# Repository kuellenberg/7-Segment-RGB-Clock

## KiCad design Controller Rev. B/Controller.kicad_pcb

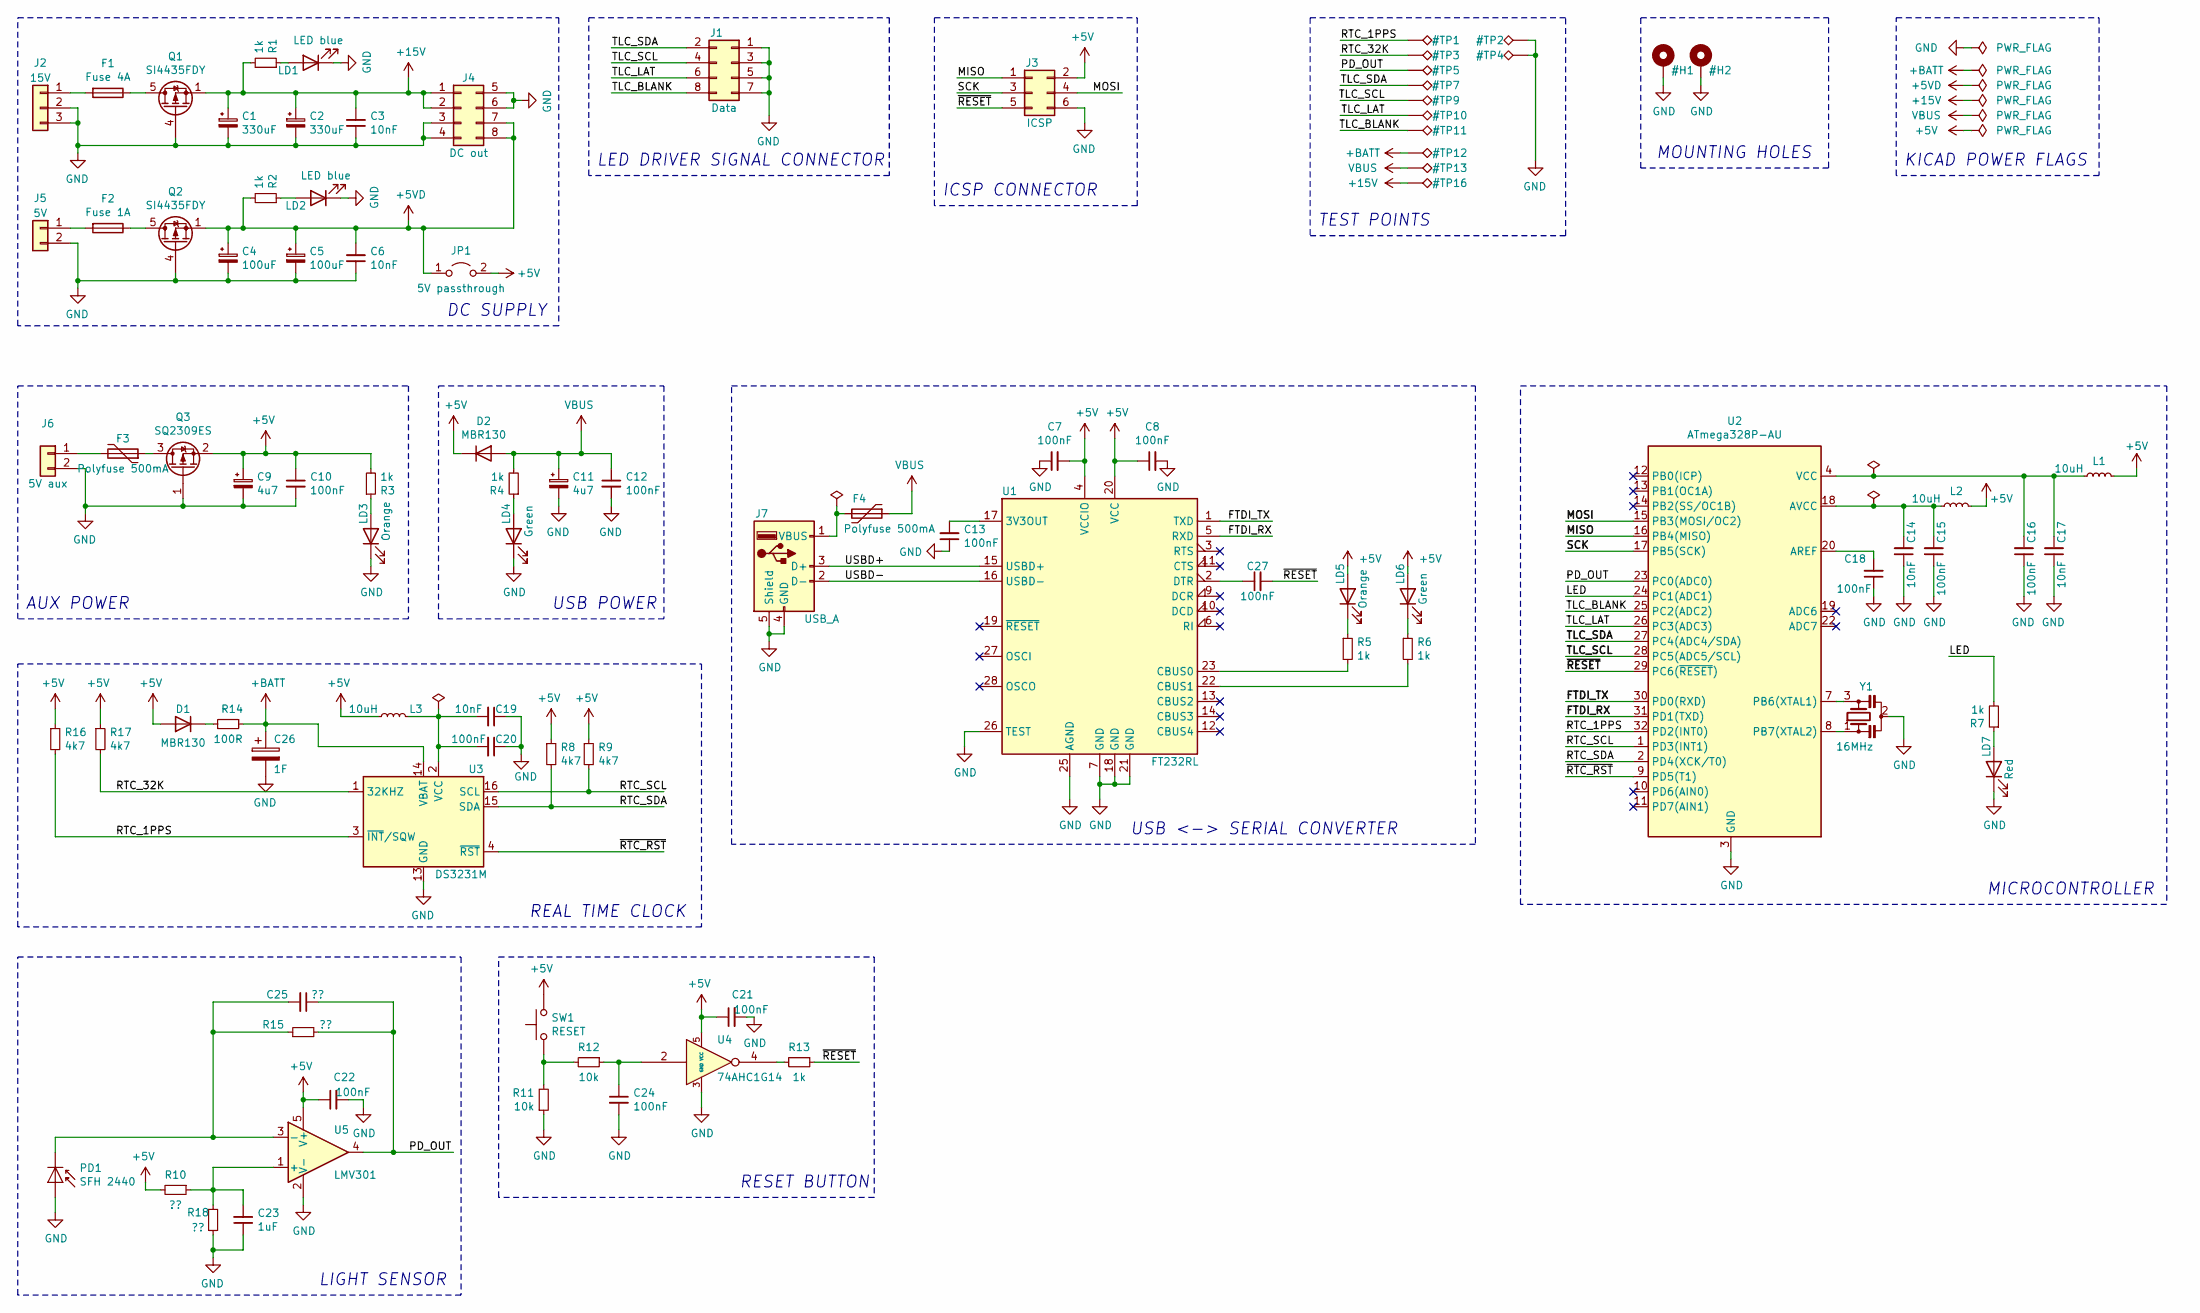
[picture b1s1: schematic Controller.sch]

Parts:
C1, C2: 330uF; CP_Elec_10x10; Mouser 661-EMVE250ADA331MJA
C3: 10nF; C_0805_2012Metric; Mouser 710-885012207092
C4, C5: 100uF; C_Elec_6.3x5.8; Mouser 647-UUR1A101MCL1GS
C6, C14, C17, C19: 10nF; C_0603_1608Metric; Mouser 710-885012206089
C7, C8, C10, C12, C13, C15, C16, C18, C20, C21, C22, C24, C27: 100nF; C_0603_1608Metric; Mouser 576-1812L050PR
C9, C11: 4u7; C_Elec_4x5.8; Mouser 667-EEE-FK1K4R7P
C23: 1uF; C_0603_1608Metric; Mouser 963-TMK107B7105MA-T
C25: ??; C_0603_1608Metric
C26: 1F; FC0H105ZFTBR44; Mouser 80-FC0H105ZFTBR44-SS
D1, D2: MBR130; D_SOD-123; Mouser 863-MBR130T1G
F1: Fuse 4A; Fuseholder_SMD_Littelfuse_154; Mouser 576-0154004.DRT
F2: Fuse 1A; Fuseholder_SMD_Littelfuse_154; Mouser 576-0154001.DR
F3, F4: Polyfuse 500mA; Fuse_1812_4532Metric; Mouser 576-1812L050PR
J1, J4: Conn_02x04_Top_Bottom; HARWIN_M20-8890845; Mouser 855-M20-8890845
J2: 15V; JST_XH_B03B-XH-A_03x2.50mm_Straight; Digikey 455-2248-ND
J3: Conn_02x03_Top_Bottom; IDC-Header_2x03_P2.54mm_Vertical; Digikey 732-5394-ND
J5: 5V; JST_XH_B2B-XH-A_1x02_P2.50mm_Vertical; Digikey 455-2247-ND
J6: Conn_01x02; JST_XH_B2B-XH-A_1x02_P2.50mm_Vertical; Digikey 455-2247-ND
J7: USB_A; USB_B_OST_USB-B1HSxx_Horizontal; Mouser 649-61729-0011BLF
JP1: Jumper; PinSocket_1x02_P2.54mm_Vertical; Digikey S1012EC-02-ND
L1, L2, L3: 10uH; L_0805_2012Metric; Mouser 963-LBR2012T100K
LD1, LD2: LED blue; LED_0603_1608Metric; Mouser 859-LTSTC193TBKT5A
LD3, LD5: LED; LED_0603_1608Metric; Mouser 859-LTST-C191KFKT
LD4, LD6: LED; LED_0603_1608Metric; Mouser 859-LTST-C190KGKT
LD7: LED; LED_0603_1608Metric; Mouser 859-LTST-C190KRKT
PD1: SFH 2440; Osram_SMD-DIL2_4.5x4.0mm; Mouser 720-SFH2440
Q1, Q2: SI4435FDY; SO-8_5.3x6.2mm_P1.27mm; Mouser 78-SI4435FDY-T1-GE3
Q3: SQ2309ES; SOT-23; Mouser 781-SQ2309ES-T1_GE3
R1, R2, R3, R4, R5, R6, R7, R13: 1k; R_0603_1608Metric; Mouser 660-RN73H1JT1001F100
R8, R9, R16, R17: 4k7; R_0603_1608Metric; Mouser 660-RN73H1JT4701F100
R10, R15, R18: ??; R_0603_1608Metric
R11, R12: 10k; R_0603_1608Metric; Mouser 660-RN73H1JTD1002F50
R14: 100R; R_0603_1608Metric; Mouser 660-RN73H1JT1000F100
SW1: RESET; SW_PUSH_6mm
U1: FT232RL; SSOP-28_5.3x10.2mm_P0.65mm; Mouser 895-FT232RL
U2: ATmega328P-AU; TQFP-32_7x7mm_P0.8mm; Mouser 556-ATMEGA328P-AU
U3: DS3231M; SOIC-16W_7.5x10.3mm_P1.27mm; Mouser 700-DS3231M+TRL
U4: 74AHC1G14; SOT-23-5; Mouser 595-SN74AHC1G14DBVR
U5: LMV301; SOT-353_SC-70-5; Mouser 926-LMV301MGX/NOPB
Y1: 16MHz; CSTNE; Mouser 81-CSTNE16M0V53Z000R

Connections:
+5V: C7.2, C8.1, C9.1, C10.1, C21.1, C22.1, D1.2 (A), D2.1 (K), J3.2, JP1.2 (B), L1.2, L2.2, L3.1, LD5.2 (A), LD6.2 (A), Q3.2 (S), R3.2, R8.1, R9.1, R10.2, R16.1, R17.1, SW1.2, U1.4 (VCCIO), U1.20 (VCC), U4.5 (VCC), U5.5 (V+)
+5VD: C4.1, C5.1, C6.2, J4.7, J4.8, JP1.1 (A), Q2.1 (S), Q2.2 (S), Q2.3 (S), R2.2
+15V: C1.1, C2.1, C3.2, J4.1, J4.2, Q1.1 (S), Q1.2 (S), Q1.3 (S), R1.2; also elsewhere on the board
+BATT: C26.1, R14.1, U3.14 (VBAT); also elsewhere on the board
/FTDI_RX: U1.5 (RXD), U2.31 (PD1(TXD))
/FTDI_TX: U1.1 (TXD), U2.30 (PD0(RXD))
/LED: R7.2, U2.24 (PC1(ADC1))
/MISO: J3.1, U2.16 (PB4(MISO))
/MOSI: J3.4, U2.15 (PB3(MOSI/OC2))
/PD_OUT: C25.1, R15.2, U2.23 (PC0(ADC0)), U5.4; also elsewhere on the board
/RTC_1PPS: R16.2, U2.32 (PD2(INT0)), U3.3 (~INT~/SQW); also elsewhere on the board
/RTC_32K: R17.2, U3.1 (32KHZ); also elsewhere on the board
/RTC_SCL: R9.2, U2.1 (PD3(INT1)), U3.16 (SCL)
/RTC_SDA: R8.2, U2.2 (PD4(XCK/T0)), U3.15 (SDA)
/SCK: J3.3, U2.17 (PB5(SCK))
/TLC_BLANK: J1.8, U2.25 (PC2(ADC2)); also elsewhere on the board
/TLC_LAT: J1.6, U2.26 (PC3(ADC3)); also elsewhere on the board
/TLC_SCL: J1.4, U2.28 (PC5(ADC5/SCL)); also elsewhere on the board
/TLC_SDA: J1.2, U2.27 (PC4(ADC4/SDA)); also elsewhere on the board
/USBD+: J7.3 (D+), U1.15 (USBD+)
/USBD-: J7.2 (D-), U1.16 (USBD-)
/~RESET~: C27.2, J3.5, R13.1, U2.29 (PC6(~RESET~))
/~RTC_RST~: U2.9 (PD5(T1)), U3.4 (~RST)
GND: C1.2, C2.2, C3.1, C4.2, C5.2, C6.1, C7.1, C8.2, C9.2, C10.2, C11.2, C12.2, C13.1, C14.1, C15.1, C16.1, C17.1, C18.1, C19.1, C20.1, C21.2, C22.2, C23.1, C24.2, C26.2, J1.1, J1.3, J1.5, J1.7, J2.2, J2.3, J3.6, J4.3, J4.4, J4.5, J4.6, J5.2, J6.2, J7.4 (GND), J7.5 (Shield), LD1.1 (K), LD2.1 (K), LD3.1 (K), LD4.1 (K), LD7.1 (K), PD1.2 (A), Q1.4 (G), Q2.4 (G), Q3.1 (G), R11.1, R18.2, U1.7 (GND), U1.18 (GND), U1.21 (GND), U1.25 (AGND), U1.26 (TEST), U2.3 (GND), U2.5 (GND), U2.21 (GND), U3.5 (GND), U3.6 (GND), U3.7 (GND), U3.8 (GND), U3.9 (GND), U3.10 (GND), U3.11 (GND), U3.12 (GND), U3.13 (GND), U4.3 (GND), U5.2 (V-), Y1.2; also elsewhere on the board
unnamed: C13.2, U1.17 (3V3OUT)
unnamed: C14.2, C15.2, L2.1, U2.18 (AVCC)
unnamed: C16.2, C17.2, L1.1, U2.4 (VCC), U2.6 (VCC)
unnamed: C18.2, U2.20 (AREF)
unnamed: C19.2, C20.2, L3.2, U3.2 (VCC)
unnamed: C23.2, R10.1, R18.1, U5.1 (+)
unnamed: C24.1, R12.1, U4.2
unnamed: C25.2, PD1.1 (K), R15.1, U5.3 (-)
unnamed: C27.1, U1.2 (DTR)
unnamed: D1.1 (K), R14.2
unnamed: F1.1, Q1.5 (D), Q1.6 (D), Q1.7 (D), Q1.8 (D)
unnamed: F1.2, J2.1
unnamed: F2.1, Q2.5 (D), Q2.6 (D), Q2.7 (D), Q2.8 (D)
unnamed: F2.2, J5.1
unnamed: F3.1, Q3.3 (D)
unnamed: F3.2, J6.1
unnamed: F4.2, J7.1 (VBUS)
unnamed: LD1.2 (A), R1.1
unnamed: LD2.2 (A), R2.1
unnamed: LD3.2 (A), R3.1
unnamed: LD4.2 (A), R4.1
unnamed: LD5.1 (K), R5.1
unnamed: LD6.1 (K), R6.1
unnamed: LD7.2 (A), R7.1
unnamed: R5.2, U1.23 (CBUS0)
unnamed: R6.2, U1.22 (CBUS1)
unnamed: R11.2, R12.2, SW1.1
unnamed: R13.2, U4.4
unnamed: U2.7 (PB6(XTAL1)), Y1.3
unnamed: U2.8 (PB7(XTAL2)), Y1.1
VBUS: C11.1, C12.1, D2.2 (A), F4.1, R4.2; also elsewhere on the board

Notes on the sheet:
REAL TIME CLOCK
USB <-> SERIAL CONVERTER
MICROCONTROLLER
ICSP CONNECTOR
USB POWER
MOUNTING HOLES
AUX POWER
DC SUPPLY
LED DRIVER SIGNAL CONNECTOR
TEST POINTS
KICAD POWER FLAGS
RESET BUTTON
LIGHT SENSOR

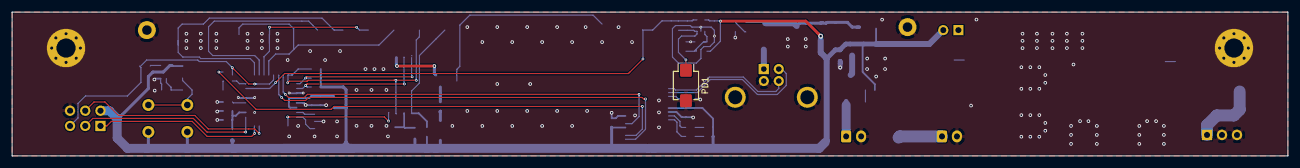
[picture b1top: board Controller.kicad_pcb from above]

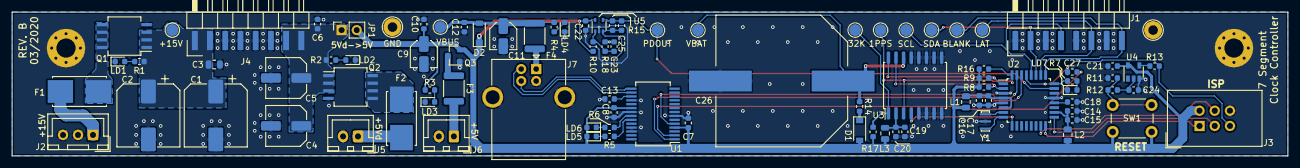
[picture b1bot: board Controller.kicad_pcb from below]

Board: 2 copper layers, 213.0 x 24.0 mm, 94 parts (91 on the bottom side), 55 nets.

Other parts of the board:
H1, H2: Mounting Hole; MountingHole_3.2mm_M3_Pad_Via
TP1: RTC_1PPS; TestPoint_Pad_D2.0mm
TP2, TP4: GND; TestPoint_Loop_D2.60mm_Drill1.6mm_Beaded
TP3: RTC_32K; TestPoint_Pad_D2.0mm
TP5: PD_OUT; TestPoint_Pad_D2.0mm
TP7: TLC_SDA; TestPoint_Pad_D2.0mm
TP9: TLC_SCL; TestPoint_Pad_D2.0mm
TP10: TLC_LAT; TestPoint_Pad_D2.0mm
TP11: TLC_BLANK; TestPoint_Pad_D2.0mm
TP12: +BATT; TestPoint_Pad_D2.0mm
TP13: VBUS; TestPoint_Pad_D2.0mm
TP16: +15V; TestPoint_Pad_D2.0mm

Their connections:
+15V: TP16.1; also elsewhere on the board
+BATT: TP12.1; also elsewhere on the board
/PD_OUT: TP5.1; also elsewhere on the board
/RTC_1PPS: TP1.1; also elsewhere on the board
/RTC_32K: TP3.1; also elsewhere on the board
/TLC_BLANK: TP11.1; also elsewhere on the board
/TLC_LAT: TP10.1; also elsewhere on the board
/TLC_SCL: TP9.1; also elsewhere on the board
/TLC_SDA: TP7.1; also elsewhere on the board
GND: H1.1, H2.1, TP2.1, TP4.1; also elsewhere on the board
VBUS: TP13.1; also elsewhere on the board

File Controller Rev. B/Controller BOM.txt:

Reference, Quantity, Value, Footprint, Datasheet, Label, Mouser, Digikey
C1 C2 ,2,"330uF","Capacitor_SMD:CP_Elec_10x10","~","","661-EMVE250ADA331MJA",""
C11 C9 ,2,"4u7","Capacitor_SMD:C_Elec_4x5.8","~","","667-EEE-FK1K4R7P",""
C13 C20 C7 C8 C18 C15 C16 C12 C10 C21 C24 C27 C22 ,13,"100nF","Capacitor_SMD:C_0603_1608Metric","~","","576-1812L050PR",""
C19 C14 C17 C6 ,4,"10nF","Capacitor_SMD:C_0603_1608Metric","~","","710-885012206089",""
C23 ,1,"1uF","Capacitor_SMD:C_0603_1608Metric","~","","963-TMK107B7105MA-T",""
C25 ,1,"??","Capacitor_SMD:C_0603_1608Metric","~"
C26 ,1,"1F","ak:FC0H105ZFTBR44","~","","80-FC0H105ZFTBR44-SS ",""
C3 ,1,"10nF","Capacitor_SMD:C_0805_2012Metric","~","","710-885012207092 ",""
C4 C5 ,2,"100uF","Capacitor_SMD:C_Elec_6.3x5.8","~","","647-UUR1A101MCL1GS ",""
D2 D1 ,2,"MBR130","Diode_SMD:D_SOD-123","~","","863-MBR130T1G ",""
F1 ,1,"Fuse 4A","ak:Fuseholder_SMD_Littelfuse_154","~","","576-0154004.DRT",""
F2 ,1,"Fuse 1A","ak:Fuseholder_SMD_Littelfuse_154","~","","576-0154001.DR",""
F4 F3 ,2,"Polyfuse 500mA","ak:Fuse_1812_4532Metric","~","","576-1812L050PR",""
J1 J4 ,2,"Conn_02x04_Top_Bottom","ak:HARWIN_M20-8890845","~","Data","855-M20-8890845 ",""
J2 ,1,"15V","Connectors_JST:JST_XH_B03B-XH-A_03x2.50mm_Straight","~","","","455-2248-ND"
J3 ,1,"Conn_02x03_Top_Bottom","Connector_IDC:IDC-Header_2x03_P2.54mm_Vertical","~","ICSP","","732-5394-ND"
J5 ,1,"5V","Connector_JST:JST_XH_B2B-XH-A_1x02_P2.50mm_Vertical","~","","","455-2247-ND"
J6 ,1,"Conn_01x02","Connector_JST:JST_XH_B2B-XH-A_1x02_P2.50mm_Vertical","~","5V aux","","455-2247-ND"
J7 ,1,"USB_A","Connector_USB:USB_B_OST_USB-B1HSxx_Horizontal"," ~","","649-61729-0011BLF",""
JP1 ,1,"Jumper","Connector_PinSocket_2.54mm:PinSocket_1x02_P2.54mm_Vertical","~","5V passthrough","","S1012EC-02-ND"
L3 L2 L1 ,3,"10uH","Inductor_SMD:L_0805_2012Metric","~","","963-LBR2012T100K",""
LD2 LD1 ,2,"LED blue","LED_SMD:LED_0603_1608Metric","~","","859-LTSTC193TBKT5A",""
LD5 LD6 LD7 LD4 LD3 ,5,"LED","LED_SMD:LED_0603_1608Metric","~","Orange","859-LTST-C191KFKT",""
PD1 ,1,"SFH 2440","OptoDevice:Osram_SMD-DIL2_4.5x4.0mm","~","","720-SFH2440 ",""
Q1 Q2 ,2,"SI4435FDY","Package_SO:SO-8_5.3x6.2mm_P1.27mm","~","","78-SI4435FDY-T1-GE3",""
Q3 ,1,"SQ2309ES","Package_TO_SOT_SMD:SOT-23","~","","781-SQ2309ES-T1_GE3",""
R12 R11 ,2,"10k","Resistor_SMD:R_0603_1608Metric","~","","660-RN73H1JTD1002F50",""
R14 ,1,"100R","Resistor_SMD:R_0603_1608Metric","~","","660-RN73H1JT1000F100",""
R15 R18 R10 ,3,"??","Resistor_SMD:R_0603_1608Metric","~"
R5 R6 R7 R4 R3 R1 R2 R13 ,8,"1k","Resistor_SMD:R_0603_1608Metric","~","","660-RN73H1JT1001F100",""
R9 R8 R16 R17 ,4,"4k7","Resistor_SMD:R_0603_1608Metric","~","","660-RN73H1JT4701F100",""
SW1 ,1,"RESET","Button_Switch_THT:SW_PUSH_6mm","~"
U1 ,1,"FT232RL","Package_SO:SSOP-28_5.3x10.2mm_P0.65mm","http://www.ftdichip.com/Products/ICs/FT232RL.htm","","895-FT232RL",""
U2 ,1,"ATmega328P-AU","Package_QFP:TQFP-32_7x7mm_P0.8mm","http://ww1.microchip.com/downloads/en/DeviceDoc/ATmega328_P%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","","556-ATMEGA328P-AU",""
U3 ,1,"DS3231M","Package_SO:SOIC-16W_7.5x10.3mm_P1.27mm","http://datasheets.maximintegrated.com/en/ds/DS3231.pdf","","700-DS3231M+TRL",""
U4 ,1,"74AHC1G14","Package_TO_SOT_SMD:SOT-23-5","","","595-SN74AHC1G14DBVR",""
U5 ,1,"LMV301","Package_TO_SOT_SMD:SOT-353_SC-70-5","","","926-LMV301MGX/NOPB",""
Y1 ,1,"16MHz","ak:CSTNE","~","","81-CSTNE16M0V53Z000R ",""

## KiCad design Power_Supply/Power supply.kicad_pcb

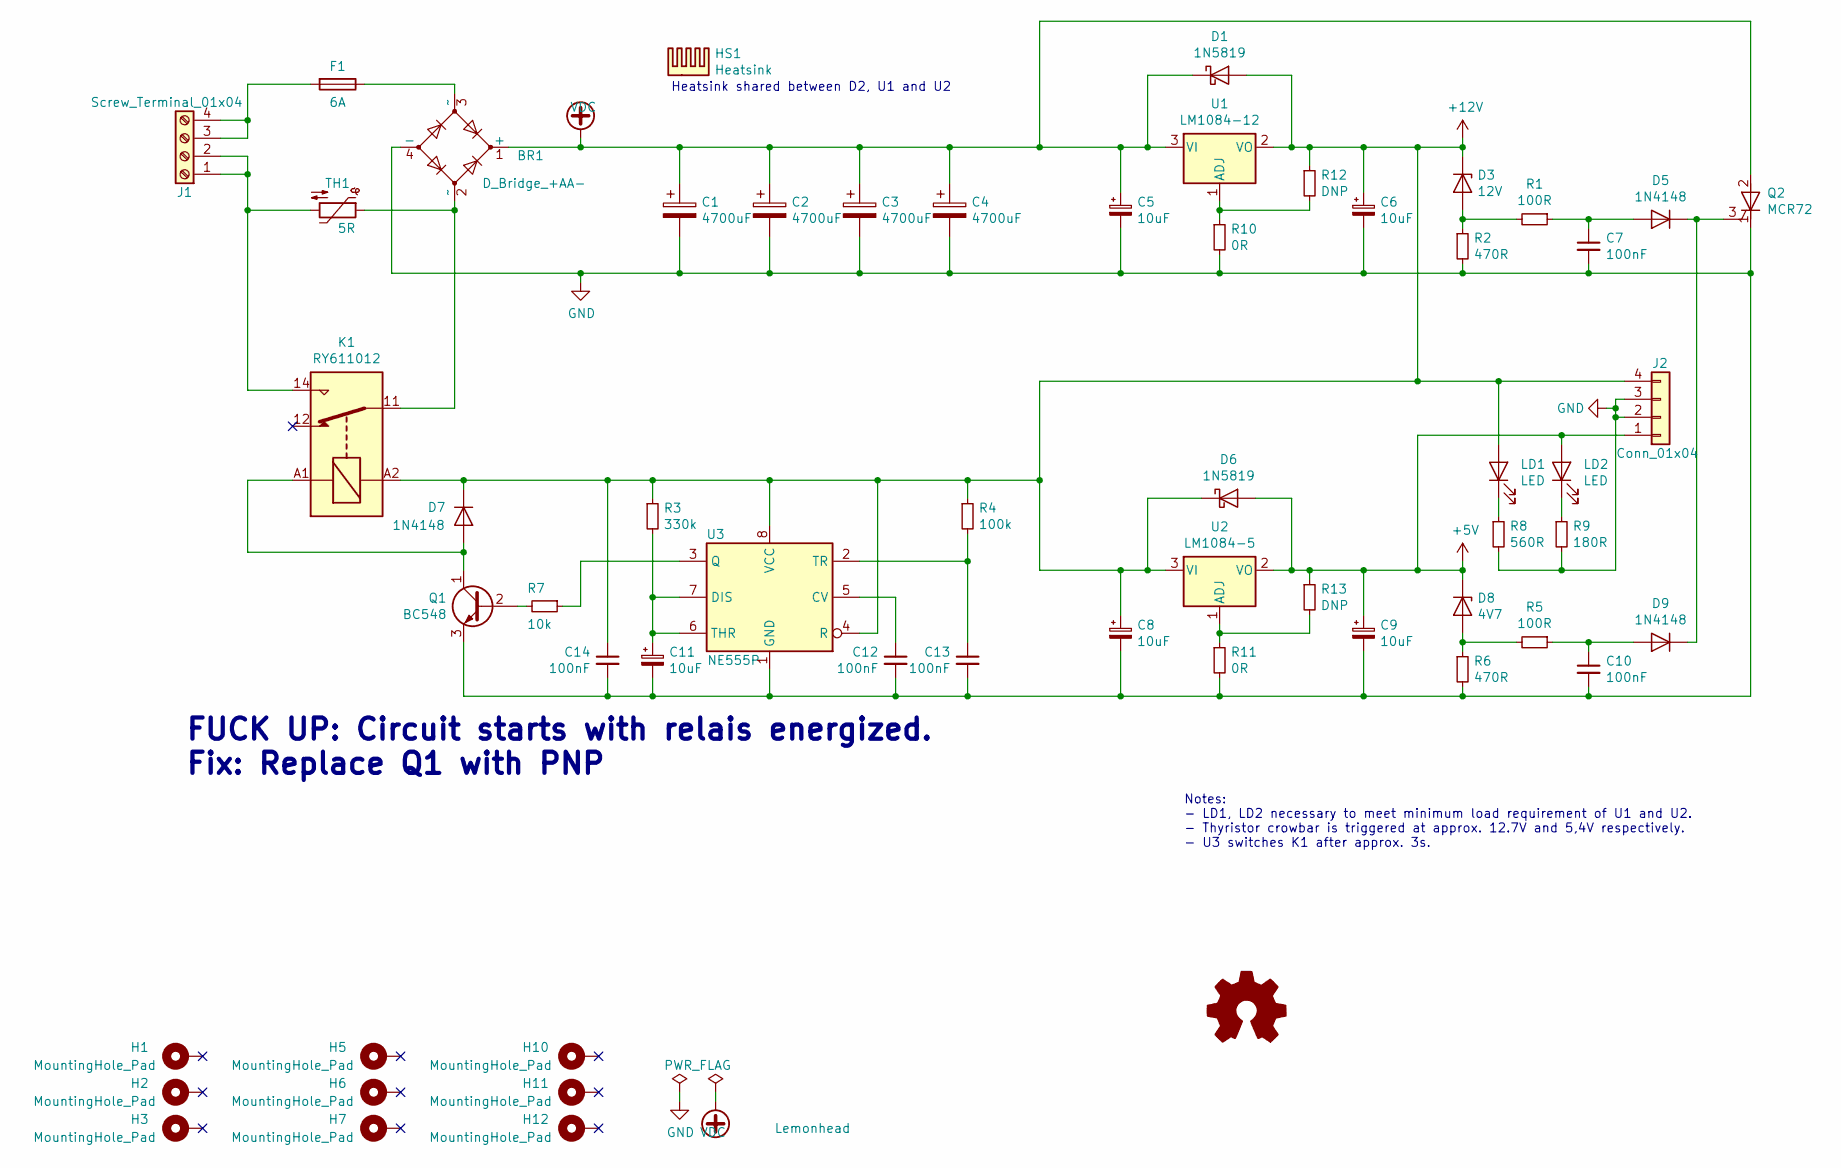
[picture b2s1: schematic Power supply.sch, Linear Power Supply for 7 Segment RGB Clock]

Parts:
BR1: D_Bridge_+AA-; GBJ
C1, C2, C3, C4: 4700uF; CP_Radial_D25.0mm_P10.00mm_SnapIn
C5, C6, C8, C9, C11: 10uF; CP_Radial_D5.0mm_P2.00mm
C7, C10, C12, C13, C14: 100nF; C_Disc_D5.0mm_W2.5mm_P2.50mm
D1, D6: 1N5819; D_DO-41_SOD81_P10.16mm_Horizontal
D3: 12V; D_DO-35_SOD27_P10.16mm_Horizontal
D5, D9: 1N4148; D_DO-35_SOD27_P10.16mm_Horizontal
D7: 1N4148; D_DO-35_SOD27_P7.62mm_Horizontal
D8: 4V7; D_DO-35_SOD27_P10.16mm_Horizontal
F1: 6A; Fuseholder_Cylinder-6.3x32mm_Schurter_0031-8002_Horizontal_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
H1, H2, H3, H5, H6, H7: MountingHole_Pad; MountingHole_3.2mm_M3_Pad
H10, H11: MountingHole_Pad; MountingHole_4.3mm_M4_Pad
H12: MountingHole_Pad; MountingHole_5.3mm_M5_Pad
HS1: Heatsink; HS-160x50
J1: Screw_Terminal_01x04; TerminalBlock_RND_205-00003_1x04_P5.00mm_Horizontal
J2: Conn_01x04; Molex_KK-396_A-41791-0004_1x04_P3.96mm_Vertical
K1: RY611012
LD1, LD2: LED; LED_D5.0mm
LOGO1: Lemonhead; lemonhead
Q1: BC548; TO-92_Inline
Q2: MCR72; TO-220F-3_Horizontal_TabDown
R1, R5: 100R; R_Axial_DIN0207_L6.3mm_D2.5mm_P10.16mm_Horizontal
R2, R6: 470R; R_Axial_DIN0207_L6.3mm_D2.5mm_P10.16mm_Horizontal
R3: 330k; R_Axial_DIN0207_L6.3mm_D2.5mm_P10.16mm_Horizontal
R4: 100k; R_Axial_DIN0207_L6.3mm_D2.5mm_P10.16mm_Horizontal
R7: 10k; R_Axial_DIN0207_L6.3mm_D2.5mm_P10.16mm_Horizontal
R8: 560R; R_Axial_DIN0207_L6.3mm_D2.5mm_P10.16mm_Horizontal
R9: 180R; R_Axial_DIN0207_L6.3mm_D2.5mm_P10.16mm_Horizontal
R10, R11: 0R; R_Axial_DIN0207_L6.3mm_D2.5mm_P10.16mm_Horizontal
R12, R13: DNP; R_Axial_DIN0207_L6.3mm_D2.5mm_P10.16mm_Horizontal
TH1: 5R; RV_Disc_D21.5mm_W6.1mm_P7.5mm
U1: LM1084-12; TO-220-3_Vertical
U2: LM1084-5; TO-220-3_Vertical
U3: NE555P; DIP-8_W7.62mm

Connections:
+5V: C9.1, D6.2 (A), D8.1 (K), J2.1, LD2.2 (A), R13.1, U2.2 (VO)
+12V: C6.1, C8.1, C14.1, D1.2 (A), D3.1 (K), D6.1 (K), D7.1 (K), J2.4, K1.A2, LD1.2 (A), R3.1, R4.1, R12.1, U1.2 (VO), U2.3 (VI), U3.4 (R), U3.8 (VCC)
GND: BR1.4 (-), C1.2, C2.2, C3.2, C4.2, C5.2, C6.2, C7.2, C8.2, C9.2, C10.2, C11.2, C12.2, C13.2, C14.2, J2.2, J2.3, Q1.3 (E), Q2.1 (K), R2.2, R6.2, R8.2, R9.2, R10.2, R11.2, U3.1 (GND)
unnamed: BR1.2 (~~), K1.11, TH1.1
unnamed: BR1.3 (~~), F1.1
unnamed: C7.1, D5.2 (A), R1.1
unnamed: C10.1, D9.2 (A), R5.1
unnamed: C11.1, R3.2, U3.6 (THR), U3.7 (DIS)
unnamed: C12.1, U3.5 (CV)
unnamed: C13.1, R4.2, U3.2 (TR)
unnamed: D3.2 (A), R1.2, R2.1
unnamed: D5.1 (K), D9.1 (K), Q2.3 (G)
unnamed: D7.2 (A), K1.A1, Q1.1 (C)
unnamed: D8.2 (A), R5.2, R6.1
unnamed: F1.2, J1.3, J1.4
unnamed: J1.1, J1.2, K1.14, TH1.2
unnamed: LD1.1 (K), R8.1
unnamed: LD2.1 (K), R9.1
unnamed: Q1.2 (B), R7.2
unnamed: R7.1, U3.3 (Q)
unnamed: R10.1, R12.2, U1.1 (ADJ)
unnamed: R11.1, R13.2, U2.1 (ADJ)
VDC: BR1.1 (+), C1.1, C2.1, C3.1, C4.1, C5.1, D1.1 (K), Q2.2 (A), U1.3 (VI)

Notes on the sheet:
Heatsink shared between D2, U1 and U2
Notes: - LD1, LD2 necessary to meet minimum load requirement of U1 and U2. - Thyristor crowbar is triggered at approx. 12.7V and 5,4V respectively. - U3 switches K1 after approx. 3s.
FUCK UP: Circuit starts with relais energized. Fix: Replace Q1 with PNP

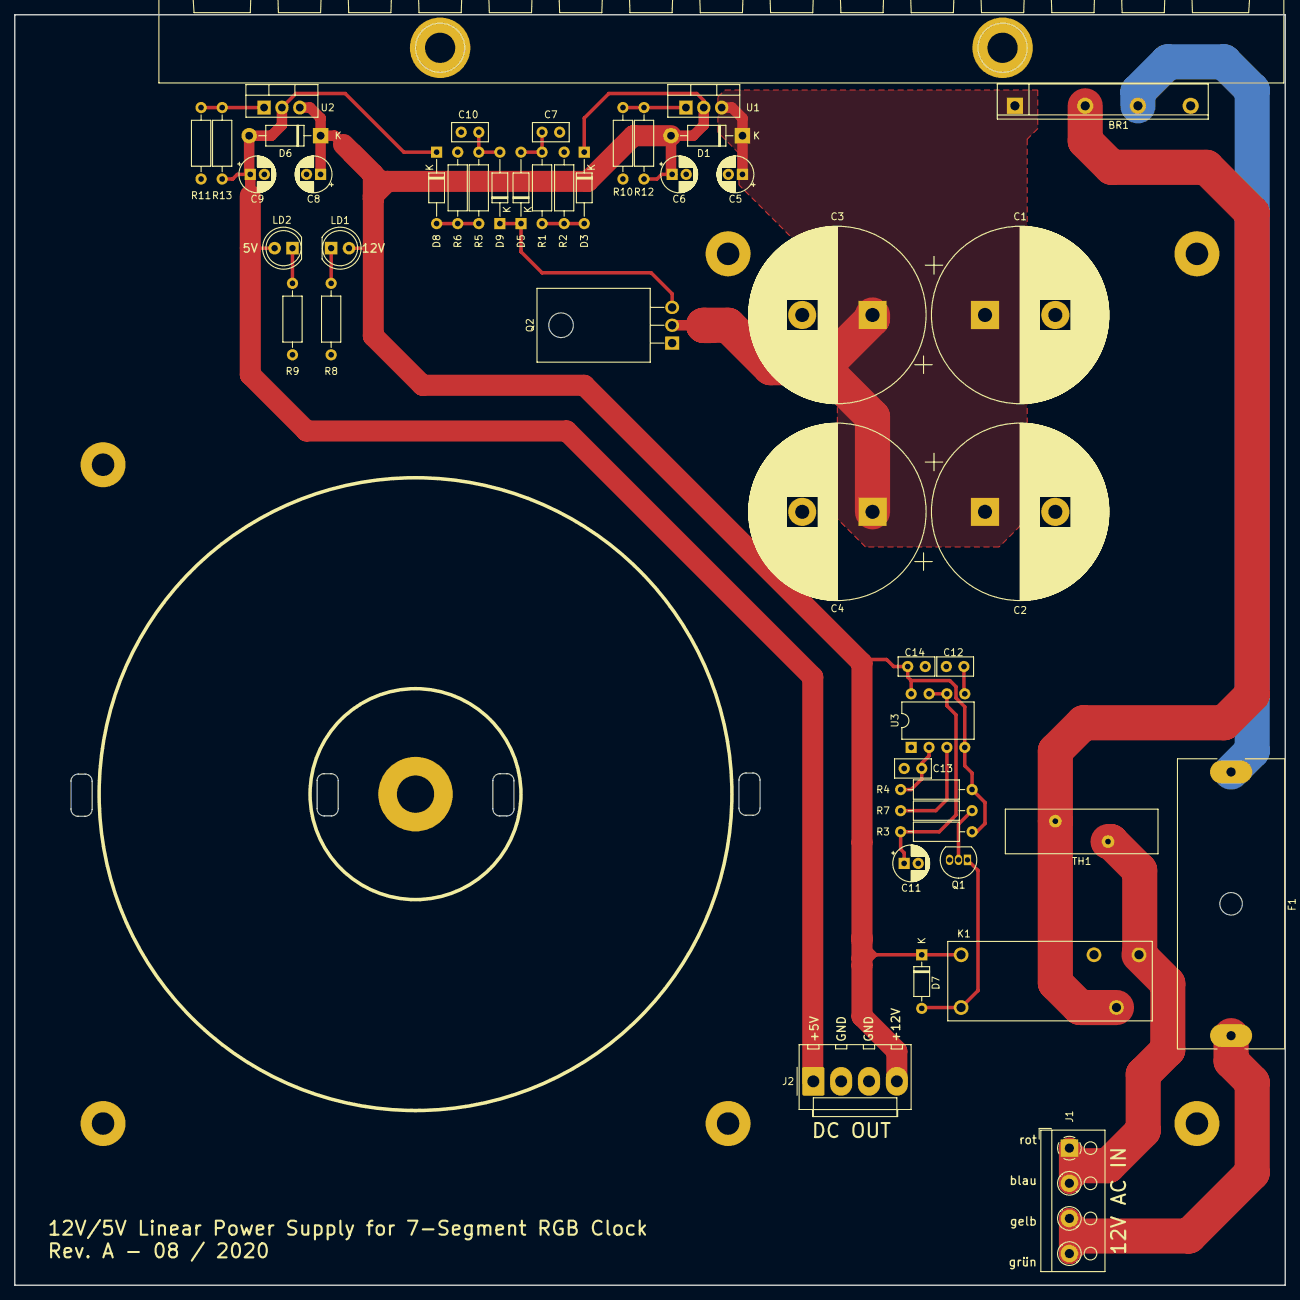
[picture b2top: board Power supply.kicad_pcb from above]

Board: 2 copper layers, 180.7 x 180.7 mm, 58 parts (0 on the bottom side), 23 nets.
